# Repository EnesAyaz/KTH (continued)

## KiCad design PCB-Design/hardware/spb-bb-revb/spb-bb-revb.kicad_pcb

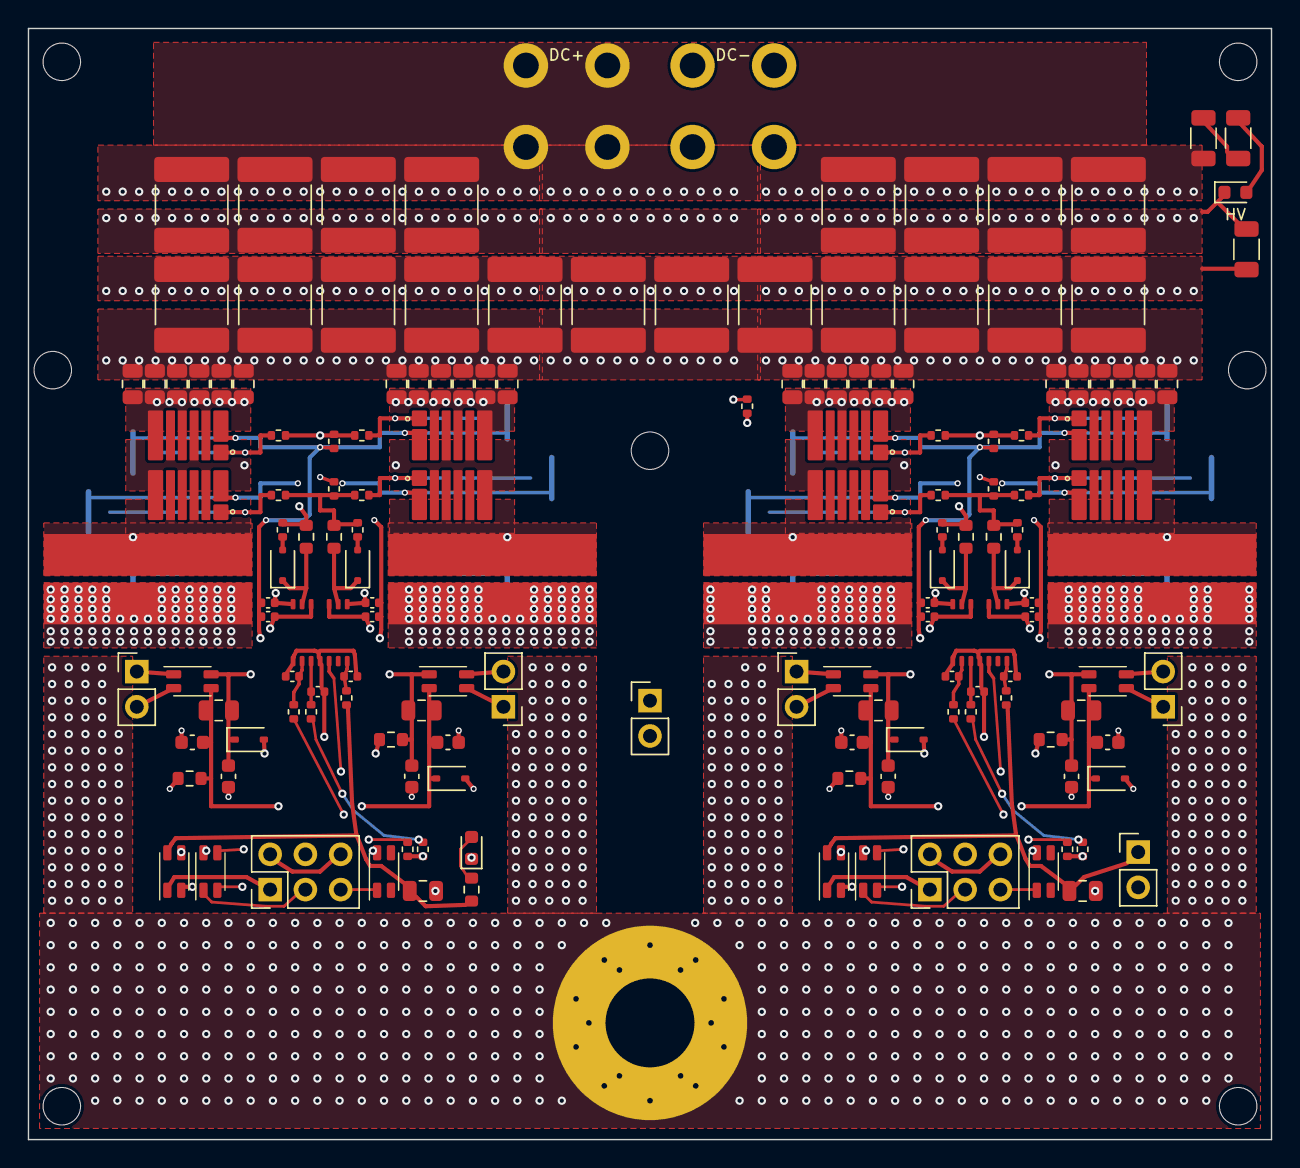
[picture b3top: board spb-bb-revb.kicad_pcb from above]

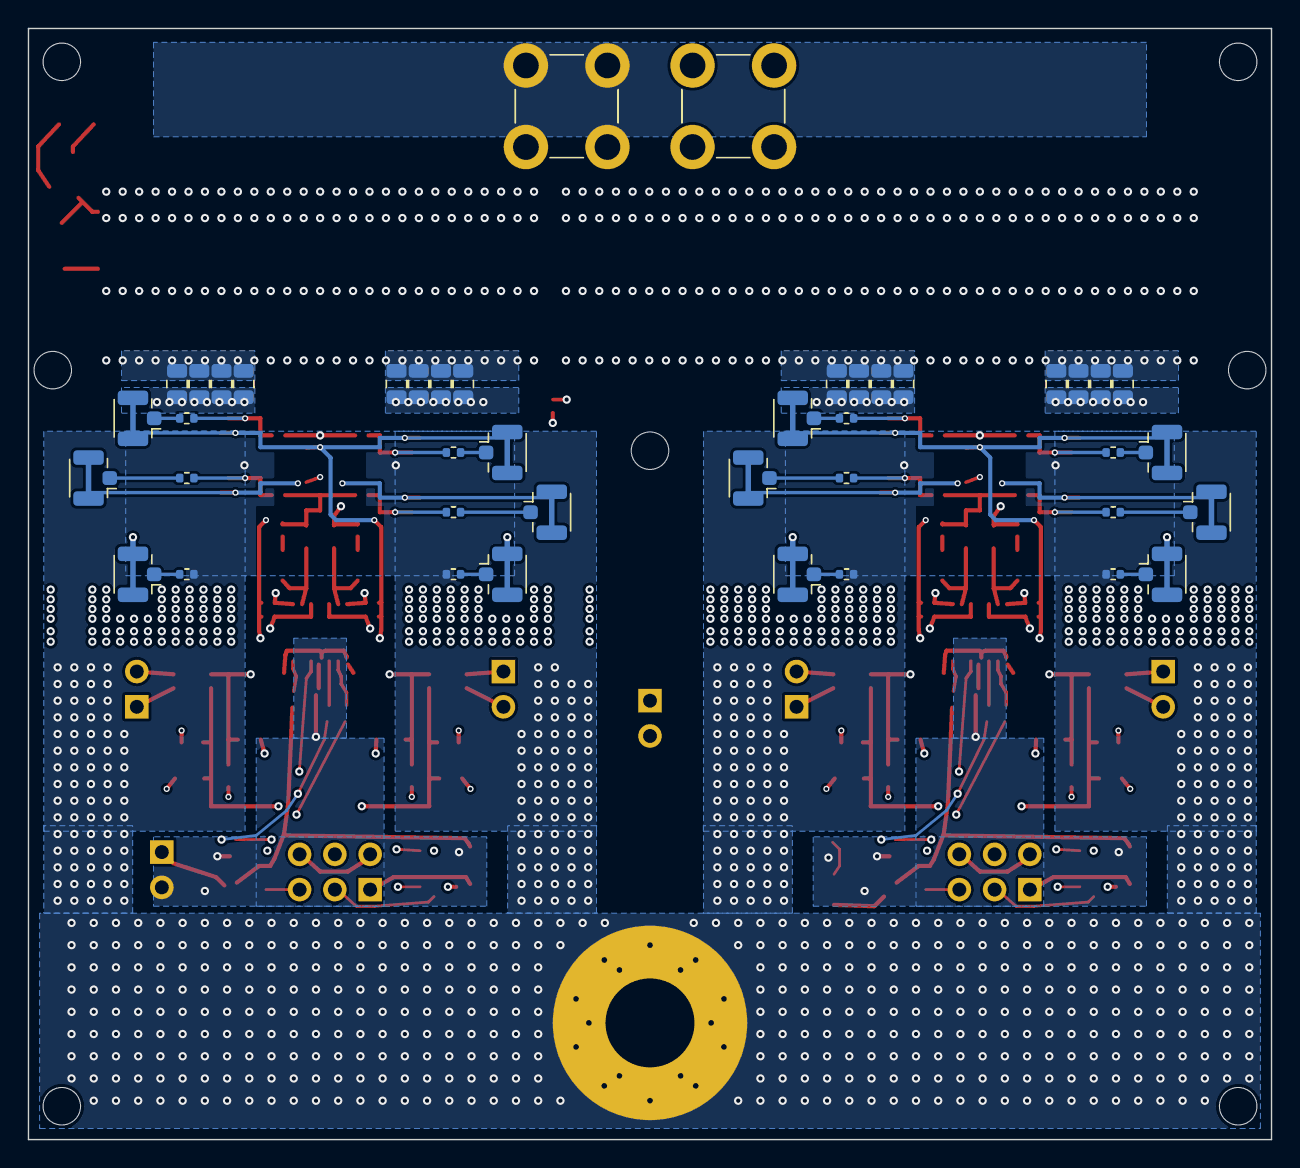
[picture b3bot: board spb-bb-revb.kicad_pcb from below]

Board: 4 copper layers, 89.5 x 80.0 mm, 204 parts (42 on the bottom side), 89 nets.

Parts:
C1, C2, C3, C4, C5, C6, C7, C8, C9, C10, C11, C12, C27, C28, C29, C30, C31, C32, C33, C34, C35, C36, C37, C38, C39, C40, C41, C42, C43, C44, C45, C46, C61, C62, C63, C64, C65, C66, C67, C68: 1uF 100V X7S; C_0805_2012Metric_TightCrtYd
C13, C14, C15, C16, C47, C48, C49, C50: 1uF 16V X7R 0402; C_0402_1005Metric
C17, C18, C51, C52: 100pF C0G 0402; C_0402_1005Metric
C19, C53: 22nF 25V X7R 0402; C_0402_1005Metric
C20, C23, C54, C57: 4.7uF 25V X7R 0805; C_0805_2012Metric
C21, C22, C24, C25, C55, C56, C58, C59: 4.7uF 16V X5R 0603; C_0603_1608Metric
C26, C60: 4.7uF 25V X7R 0805 (12 V); C_0805_2012Metric
C69, C70, C71, C72, C73, C74, C75, C76, C77, C78, C79, C80, C81, C82, C83, C84, C85, C86, C87, C88: 22uF 100V X7S 2220; C_2220_5750Metric_TightCrtYd
D1, D2, D6, D7: PMEG3020EJ; D_SOD-323F
D3, D4, D8, D9: BZX384-C5V1; D_SOD-323
D5: green 0603 (12 V); LED_0603_1608Metric
D10: red 0603 (DC link present); LED_0603_1608Metric
H1, H2, H3, H4: M2.5 insulated; MountingHole_2.7mm_M2.5
H5, H6, H7: M2.5 heatsink spreader; MountingHole_2.7mm_M2.5
HS1: Fischer LAM 4 (100 mm) + spreader; HS_LAM4K10012_revb
J1: DC+; Wuerth_REDCUBE-THR_WP-THRBU_74650174_THR
J2: DC-; Wuerth_REDCUBE-THR_WP-THRBU_74650174_THR
J3, J12: V_ISO,HS in: 1 +, 2 -; PinHeader_1x02_P2.54mm_Vertical
J4, J13: V_ISO,LS in: 1 +, 2 -; PinHeader_1x02_P2.54mm_Vertical
J5: CTRL1: 1 12V 2 GND 3 PWM_H 4 PWM_L 5 DIS 6 GND; PinHeader_2x03_P2.54mm_Vertical
J6: U.FL H1; U.FL_Hirose_U.FL-R-SMT-1_Vertical
J7: U.FL L1; U.FL_Hirose_U.FL-R-SMT-1_Vertical
J8: U.FL D1; U.FL_Hirose_U.FL-R-SMT-1_Vertical
J9: U.FL H2; U.FL_Hirose_U.FL-R-SMT-1_Vertical
J10: U.FL L2; U.FL_Hirose_U.FL-R-SMT-1_Vertical
J11: U.FL D2; U.FL_Hirose_U.FL-R-SMT-1_Vertical
J14: CTRL2: 1 12V 2 GND 3 PWM_H 4 PWM_L 5 DIS 6 GND; PinHeader_2x03_P2.54mm_Vertical
J15: FAN 12V: 1 +12V, 2 GND; PinHeader_1x02_P2.54mm_Vertical
J16: U.FL H3; U.FL_Hirose_U.FL-R-SMT-1_Vertical
J17: U.FL L3; U.FL_Hirose_U.FL-R-SMT-1_Vertical
J18: U.FL D3; U.FL_Hirose_U.FL-R-SMT-1_Vertical
J19: U.FL H4; U.FL_Hirose_U.FL-R-SMT-1_Vertical
J20: U.FL L4; U.FL_Hirose_U.FL-R-SMT-1_Vertical
J21: U.FL D4; U.FL_Hirose_U.FL-R-SMT-1_Vertical
J22: AC; AC_BOLT_M6
J23: 1:NTC 2:DC- (LS domain!); PinHeader_1x02_P2.54mm_Vertical
L1, L2, L3, L4, L5, L6, L7, L8, L9, L10: WE-CNSW 744232601; L_CommonMode_Wurth_WE-CNSW-1206
Q1, Q2, Q3, Q4, Q5, Q6, Q7, Q8: EPC2361
R1, R25: 0R5 1% (R_G HL); R_0402_1005Metric
R2, R26: 0R5 1% (R_G HR); R_0402_1005Metric
R3, R27: 0R5 1% (R_G LL); R_0402_1005Metric
R4, R28: 0R5 1% (R_G LR); R_0402_1005Metric
R5, R29: 10k 1% (HS gate pull-down); R_0402_1005Metric
R6, R30: 10k 1% (LS gate pull-down); R_0402_1005Metric
R7, R31: 0R75 1% (R_ON,A); R_0603_1608Metric
R8, R32: 0R (R_OFF,A); R_0402_1005Metric
R9, R33: 0R75 1% (R_ON,B); R_0603_1608Metric
R10, R34: 0R (R_OFF,B); R_0402_1005Metric
R11, R35: 47R 1% (INA); R_0402_1005Metric
R12, R36: 47R 1% (INB); R_0402_1005Metric
R13, R37: 3k 1% (RVDDI); R_0402_1005Metric
R14, R15, R38, R39: 150R 1% 0603 (bias, <= 82 mW); R_0603_1608Metric
R16, R40: 10k (PWM_H pull-down); R_0402_1005Metric
R17, R41: 10k (PWM_L pull-down); R_0402_1005Metric
R18: 4.7k (LED); R_0603_1608Metric
R19, R22, R42, R45: 0R (V_GS HS); R_0402_1005Metric
R20, R23, R43, R46: 0R (V_GS LS); R_0402_1005Metric
R21, R24, R44, R47: 953R 1% (V_DS LS, 20:1 into 50 R); R_0402_1005Metric
R48, R49: 68k 1206 (HV LED); R_1206_3216Metric
R50: 100k 1206 (bleeder); R_1206_3216Metric
RS1, RS2, RS3, RS4: UFCS-R001; PMK_UFCS_R001
RT1: NTC 10k B3380; R_0402_1005Metric
U1, U2: 2EDF7275K; 2EDF7275K_PG-TFLGA-13-4

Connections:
+12V1: C26.1, L3.2, R13.1, R18.1
+12V2: C60.1, J15.1, L8.2, R37.1
C_12V1: J5.1, L3.1
C_12V2: J14.1, L8.1
C_DIS1: J5.5, L5.1
C_DIS2: J14.5, L10.1
C_GND1: J5.2, J5.6, L3.4
C_GND2: J14.2, J14.6, L8.4
C_PWMH1: J5.3, L4.1
C_PWMH2: J14.3, L9.1
C_PWML1: J5.4, L4.4
C_PWML2: J14.4, L9.4
DCN: C1.2, C2.2, C3.2, C4.2, C5.2, C6.2, C7.2, C8.2, C9.2, C10.2, C11.2, C12.2, C27.1, C28.1, C29.1, C30.1, C31.1, C32.1, C33.1, C34.1, C35.2, C36.2, C37.2, C38.2, C39.2, C40.2, C41.2, C42.2, C43.2, C44.2, C45.2, C46.2, C61.1, C62.1, C63.1, C64.1, C65.1, C66.1, C67.1, C68.1, C69.1, C70.1, C71.1, C72.1, C73.1, C74.1, C75.1, C76.1, C77.1, C78.1, C79.1, C80.1, C81.1, C82.1, C83.1, C84.1, C85.1, C86.1, C87.1, C88.1, D10.1, J2.1, J23.2, R50.2, RS1.2, RS2.2, RS3.2, RS4.2, RT1.1
DCP: C1.1, C2.1, C3.1, C4.1, C5.1, C6.1, C7.1, C8.1, C9.1, C10.1, C11.1, C12.1, C27.2, C28.2, C29.2, C30.2, C31.2, C32.2, C33.2, C34.2, C35.1, C36.1, C37.1, C38.1, C39.1, C40.1, C41.1, C42.1, C43.1, C44.1, C45.1, C46.1, C61.2, C62.2, C63.2, C64.2, C65.2, C66.2, C67.2, C68.2, C69.2, C70.2, C71.2, C72.2, C73.2, C74.2, C75.2, C76.2, C77.2, C78.2, C79.2, C80.2, C81.2, C82.2, C83.2, C84.2, C85.2, C86.2, C87.2, C88.2, J1.1, Q1.3, Q1.5, Q1.7, Q2.3, Q2.5, Q2.7, Q5.3, Q5.5, Q5.7, Q6.3, Q6.5, Q6.7, R48.1, R50.1
DIS1: L5.2, U1.5
DIS2: L10.2, U2.5
GH_L1: Q1.1, R1.1, R19.2
GH_L2: Q5.1, R25.1, R42.2
GH_R1: Q2.1, R2.2, R22.1
GH_R2: Q6.1, R26.2, R45.1
GH_STAR1: R1.2, R2.1, R5.2, R7.2, R8.2
GH_STAR2: R25.2, R26.1, R29.2, R31.2, R32.2
GL_L1: Q3.1, R3.1, R20.2
GL_L2: Q7.1, R27.1, R43.2
GL_R1: Q4.1, R4.2, R23.1
GL_R2: Q8.1, R28.2, R46.1
GL_STAR1: R3.2, R4.1, R6.1, R9.2, R10.2
GL_STAR2: R27.2, R28.1, R30.1, R33.2, R34.2
GNDI1: C17.1, C18.2, C19.2, C26.2, D5.1, L3.3, R16.1, R17.1, U1.1, U1.4
GNDI2: C51.1, C52.2, C53.2, C60.2, J15.2, L8.3, R40.1, R41.1, U2.1, U2.4
HVA: R48.2, R49.1
HVB: D10.2, R49.2
INA1: C17.2, R11.2, U1.2
INA2: C51.2, R35.2, U2.2
INB1: C18.1, R12.2, U1.3
INB2: C52.1, R36.2, U2.3
KH1: C13.1, C14.1, C21.1, C22.1, D3.2, J6.2, J9.2, Q1.2, Q2.2, R5.1, R14.1
KH2: C47.1, C48.1, C55.1, C56.1, D8.2, J16.2, J19.2, Q5.2, Q6.2, R29.1, R38.1
KL1: C15.2, C16.2, C24.1, C25.2, D4.2, J7.2, J10.2, Q3.2, Q4.2, R6.2, R15.1
KL2: C49.2, C50.2, C58.1, C59.2, D9.2, J17.2, J20.2, Q7.2, Q8.2, R30.2, R39.1
LEDA_12V1: D5.2, R18.2
LSRC1: J8.2, Q3.4, Q3.6, RS1.1
LSRC2: J11.2, Q4.4, Q4.6, RS2.1
LSRC3: J18.2, Q7.4, Q7.6, RS3.1
LSRC4: J21.2, Q8.4, Q8.6, RS4.1
NTC: J23.1, RT1.2
OFFA1: D1.2, R8.1
OFFA2: D6.2, R32.1
OFFB1: D2.2, R10.1
OFFB2: D7.2, R34.1
OUTA1: D1.1, R7.1, U1.12
OUTA2: D6.1, R31.1, U2.12
OUTB1: D2.1, R9.1, U1.9
OUTB2: D7.1, R33.1, U2.9
PWM_H1: L4.2, R11.1, R16.2
PWM_H2: L9.2, R35.1, R40.2
PWM_L1: L4.3, R12.1, R17.2
PWM_L2: L9.3, R36.1, R41.2
SW: J22.1, Q1.4, Q1.6, Q2.4, Q2.6, Q3.3, Q3.5, Q3.7, Q4.3, Q4.5, Q4.7, Q5.4, Q5.6, Q6.4, Q6.6, Q7.3, Q7.5, Q7.7, Q8.3, Q8.5, Q8.7, R21.2, R24.1, R44.2, R47.1
UFL_D1: J8.1, R21.1
UFL_D2: J11.1, R24.2
UFL_D3: J18.1, R44.1
UFL_D4: J21.1, R47.2
UFL_H1: J6.1, R19.1
UFL_H2: J9.1, R22.2
UFL_H3: J16.1, R42.1
UFL_H4: J19.1, R45.2
UFL_L1: J7.1, R20.1
UFL_L2: J10.1, R23.2
UFL_L3: J17.1, R43.1
UFL_L4: J20.1, R46.2
VDDA1: C13.2, C20.2, C21.2, D3.1, L1.2, U1.13
VDDA2: C47.2, C54.2, C55.2, D8.1, L6.2, U2.13
VDDB1: C16.1, C23.2, C25.1, D4.1, L2.4, U1.10
VDDB2: C50.1, C57.2, C59.1, D9.1, L7.4, U2.10
VDDI1: C19.1, R13.2, U1.7
VDDI2: C53.1, R37.2, U2.7
VEEA1: C14.2, C20.1, C22.2, L1.3, R14.2, U1.11
VEEA2: C48.2, C54.1, C56.2, L6.3, R38.2, U2.11
VEEB1: C15.1, C23.1, C24.2, L2.1, R15.2, U1.8
VEEB2: C49.1, C57.1, C58.2, L7.1, R39.2, U2.8
VINA_N1: J3.2, L1.4
VINA_N2: J12.2, L6.4
VINA_P1: J3.1, L1.1
VINA_P2: J12.1, L6.1
VINB_N1: J4.2, L2.2
VINB_N2: J13.2, L7.2
VINB_P1: J4.1, L2.3
VINB_P2: J13.1, L7.3

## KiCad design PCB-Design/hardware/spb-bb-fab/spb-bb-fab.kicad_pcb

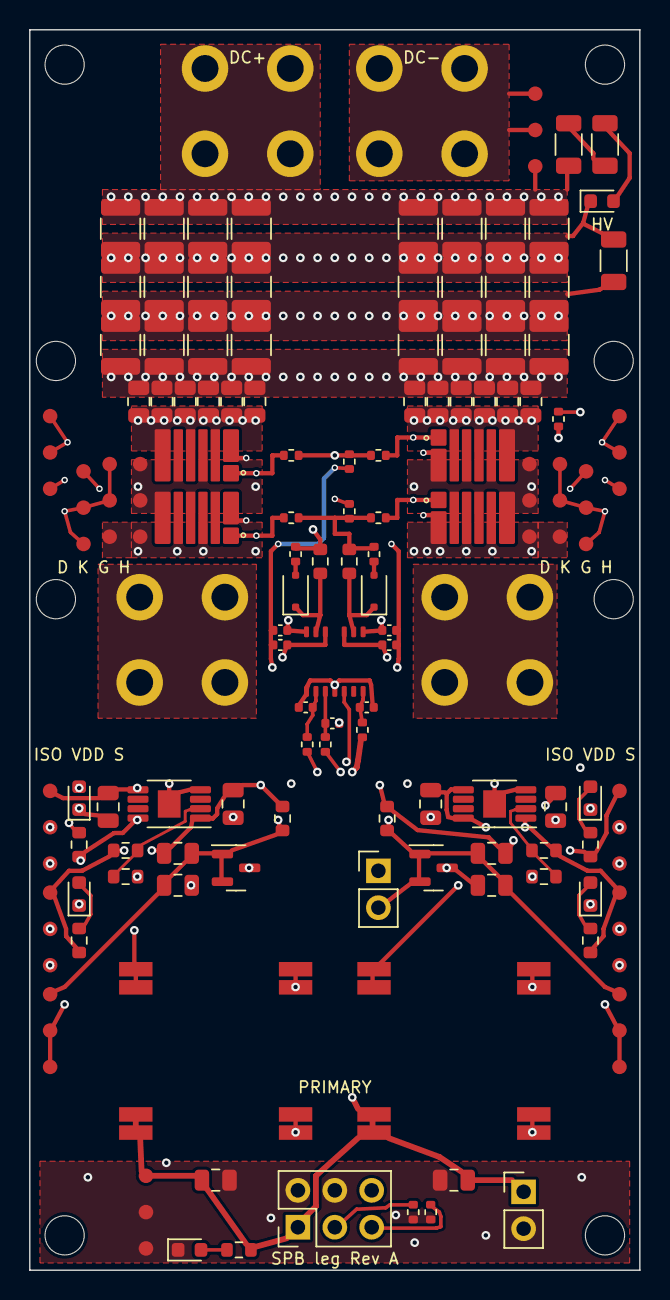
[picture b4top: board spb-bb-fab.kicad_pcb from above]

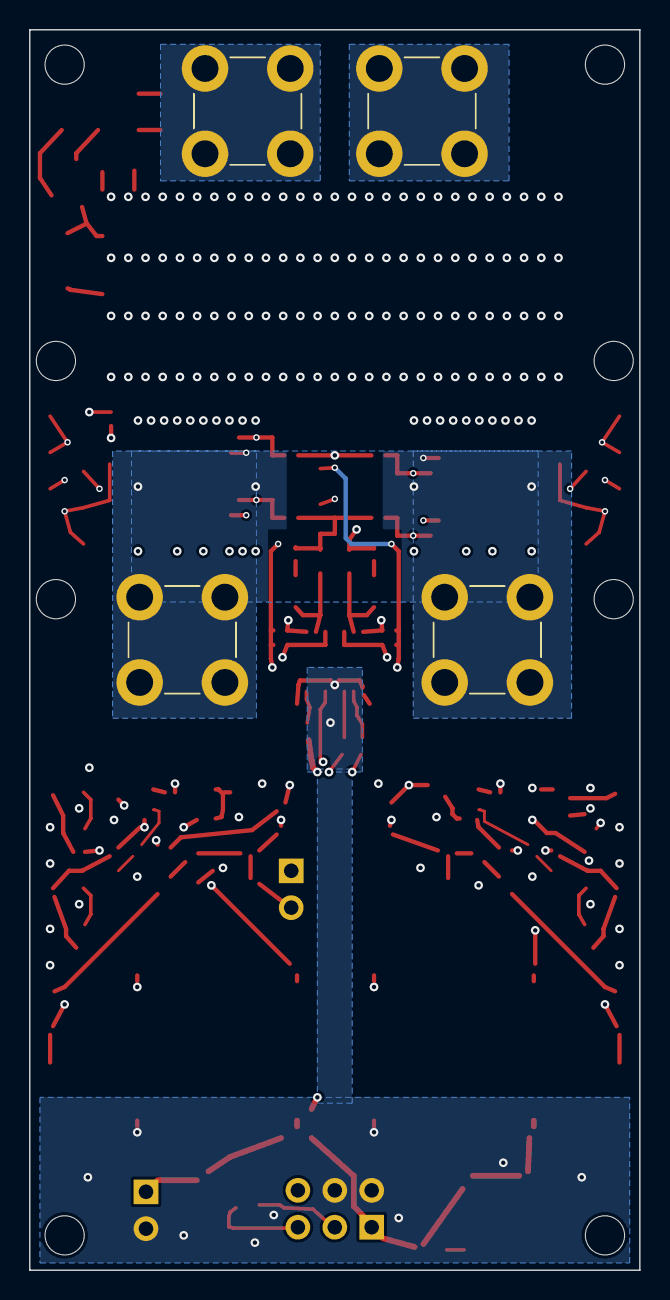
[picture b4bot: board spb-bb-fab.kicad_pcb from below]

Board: 4 copper layers, 42.0 x 85.4 mm, 134 parts (4 on the bottom side), 37 nets.

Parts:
C1, C2, C3, C4, C5, C6, C7, C8, C9, C10, C11, C12: 1uF 100V X7S; C_0805_2012Metric_TightCrtYd
C13, C14, C15, C16, C17, C18, C19, C20, C21, C22, C23, C24, C25, C26, C27, C28, C29, C30, C31, C32, C33, C34, C35, C36: 10uF 100V X7S; C_1210_3225Metric_TightCrtYd
C100, C101, C102, C103: 1uF 16V X7R 0402; C_0402_1005Metric
C104, C105: 100pF C0G 0402; C_0402_1005Metric
C106: 22nF 25V X7R 0402; C_0402_1005Metric
C107, C112: 4.7uF 25V X7R 0805; C_0805_2012Metric
C108, C113: 10uF 16V X7R 0805; C_0805_2012Metric
C109, C110, C114, C115: 4.7uF 16V X7R 0805; C_0805_2012Metric
C111, C116: 4.7uF 25V X7R 0805 (12 V in); C_0805_2012Metric
D1, D2: PMEG3020EJ; D_SOD-323F
D3: green 0603 (ISO A); LED_0603_1608Metric
D4: green 0603 (VDD A); LED_0603_1608Metric
D5: green 0603 (ISO B); LED_0603_1608Metric
D6: green 0603 (VDD B); LED_0603_1608Metric
D7: green 0603 (12 V); LED_0603_1608Metric
D8: red 0603 (DC link present); LED_0603_1608Metric
H1, H2, H3, H4: M2.5 insulated; MountingHole_2.7mm_M2.5
H5, H6, H7, H8: M2.5 heatsink; MountingHole_2.7mm_M2.5
HS1: Fischer LAM 4 K 50 12 + spreader; HS_LAM4K5012_assembly
J1: DC+; Wuerth_REDCUBE-THR_WP-THRBU_74650174_THR
J2: DC-; Wuerth_REDCUBE-THR_WP-THRBU_74650174_THR
J3, J4: AC; Wuerth_REDCUBE-THR_WP-THRBU_74650174_THR
J5: 1:+12V 2:GND 3:PWM_H 4:GND 5:PWM_L 6:DIS; PinHeader_2x03_P2.54mm_Vertical
J6: 1:NTC 2:DC- (LS domain!); PinHeader_1x02_P2.54mm_Vertical
J7: FAN 12V: 1 +12V, 2 GND; PinHeader_1x02_P2.54mm_Vertical
PS1, PS2: MGN1S1208MC; Murata_MGN1_SMD
Q1, Q2, Q3, Q4: EPC2361
R1: 0R5 1% (gate HL); R_0402_1005Metric
R2: 0R5 1% (gate HR); R_0402_1005Metric
R3: 0R5 1% (gate LL); R_0402_1005Metric
R4: 0R5 1% (gate LR); R_0402_1005Metric
R5: 0R75 1% (R_ON,A); R_0603_1608Metric
R6: 0R (R_OFF,A); R_0402_1005Metric
R7: 0R75 1% (R_ON,B); R_0603_1608Metric
R8: 0R (R_OFF,B); R_0402_1005Metric
R9: 47R 1% (INA); R_0402_1005Metric
R10: 47R 1% (INB); R_0402_1005Metric
R11: 3k 1% (RVDDI); R_0402_1005Metric
R12, R15: 102k 1%; R_0603_1608Metric
R13, R16: 23.7k 1%; R_0603_1608Metric
R14, R17: 2.2k 1% (shunt bias); R_0603_1608Metric
R30, R32: 2.7k (LED); R_0603_1608Metric
R31, R33: 1.8k (LED); R_0603_1608Metric
R34: 4.7k (LED); R_0603_1608Metric
R35: 10k (PWM_H pull-down); R_0402_1005Metric
R36: 10k (PWM_L pull-down); R_0402_1005Metric
R37, R38: 68k 1206 (HV LED); R_1206_3216Metric
R39: 100k 1206 (bleeder); R_1206_3216Metric
R41: 10k 1% (HS gate pull-down); R_0402_1005Metric
R42: 10k 1% (LS gate pull-down); R_0402_1005Metric
RT1: NTC 10k B3380; R_0402_1005Metric
TP1: D: Vds Q3; Probe_2Sig1Gnd_2.5_5.0
TP2: K: vKS Q3 (tip K); Probe_2Sig1Gnd_2.5_5.0
TP3: G: Vgs Q3; Probe_1Sig2Gnd_2.5_5.0
TP4: H: Vgs Q1 (iso); Probe_1Sig2Gnd_2.5_5.0
TP5: D: Vds Q4; Probe_2Sig1Gnd_2.5_5.0
TP6: K: vKS Q4 (tip K); Probe_2Sig1Gnd_2.5_5.0
TP7: G: Vgs Q4; Probe_1Sig2Gnd_2.5_5.0
TP8: H: Vgs Q2 (iso); Probe_1Sig2Gnd_2.5_5.0
TP9: ISO A; Probe_1Sig2Gnd_2.5_5.0
TP10: VDD A; Probe_1Sig2Gnd_2.5_5.0
TP11: S A; Probe_1Sig2Gnd_2.5_5.0
TP12: ISO B; Probe_1Sig2Gnd_2.5_5.0
TP13: VDD B; Probe_1Sig2Gnd_2.5_5.0
TP14: S B; Probe_1Sig2Gnd_2.5_5.0
TP15: 12V; Probe_1Sig2Gnd_2.5_5.0
TP16: DC link; Probe_1Sig2Gnd_2.5_5.0
U1: 2EDF7275K; 2EDF7275K_PG-TFLGA-13-4
U2, U3: TPS7A4901 6.29 V; HVSSOP-8-1EP_3x3mm_P0.65mm_EP1.57x1.89mm
U4, U5: TLV431A (1.24 V); SOT-23

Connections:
+12V: C111.1, C116.2, J5.1, J7.1, PS1.19, PS1.20, PS2.19, PS2.20, R11.1, R34.2, TP15.1
ADJA: R12.2, R13.1, U2.2
ADJB: R15.1, R16.2, U3.2
DCN: C1.2, C2.2, C3.2, C4.2, C5.2, C6.2, C7.2, C8.2, C9.2, C10.2, C11.2, C12.2, C13.1, C14.1, C15.1, C16.1, C17.1, C18.1, C19.1, C20.1, C21.2, C22.2, C23.2, C24.2, C25.2, C26.2, C27.2, C28.2, C29.1, C30.1, C31.1, C32.1, C33.1, C34.1, C35.1, C36.1, C102.2, C103.2, C114.1, C115.2, D8.1, J2.1, J6.2, Q3.2, Q3.4, Q3.6, Q4.2, Q4.4, Q4.6, R17.1, R39.2, R42.2, RT1.1, TP1.2, TP2.1, TP2.2, TP3.2, TP5.2, TP6.1, TP6.2, TP7.2, TP14.1, TP16.2, U5.1, U5.2
DCP: C1.1, C2.1, C3.1, C4.1, C5.1, C6.1, C7.1, C8.1, C9.1, C10.1, C11.1, C12.1, C13.2, C14.2, C15.2, C16.2, C17.2, C18.2, C19.2, C20.2, C21.1, C22.1, C23.1, C24.1, C25.1, C26.1, C27.1, C28.1, C29.2, C30.2, C31.2, C32.2, C33.2, C34.2, C35.2, C36.2, J1.1, Q1.3, Q1.5, Q1.7, Q2.3, Q2.5, Q2.7, R37.1, R39.1, TP16.1
DIS: J5.6, U1.5
GH_L: Q1.1, R1.1, TP4.1
GH_R: Q2.1, R2.2, TP8.1
GH_STAR: R1.2, R2.1, R5.2, R6.2, R41.2
GL_L: Q3.1, R3.1, TP3.1
GL_R: Q4.1, R4.2, TP7.1
GL_STAR: R3.2, R4.1, R7.2, R8.2, R42.1
GNDI: C104.1, C105.2, C106.2, C111.2, C116.1, D7.1, J5.2, J5.4, J7.2, PS1.1, PS1.2, PS2.1, PS2.2, R35.1, R36.1, TP15.2, U1.1, U1.4
HVA: R37.2, R38.1
HVB: D8.2, R38.2
INA: C104.2, R9.2, U1.2
INB: C105.1, R10.2, U1.3
ISOA_P: C107.2, PS1.11, PS1.12, R30.1, TP9.1, U2.5, U2.8
ISOB_P: C112.2, PS2.11, PS2.12, R32.1, TP12.1, U3.5, U3.8
LEDA_12V: D7.2, R34.1
LEDA_ISOA: D3.2, R30.2
LEDA_ISOB: D5.2, R32.2
LEDA_VDDA: D4.2, R31.2
LEDA_VDDB: D6.2, R33.2
NTC: J6.1, RT1.2
OFFA: D1.2, R6.1
OFFB: D2.2, R8.1
OUTA: D1.1, R5.1, U1.12
OUTB: D2.1, R7.1, U1.9
PWM_H: J5.3, R9.1, R35.2
PWM_L: J5.5, R10.1, R36.2
SW: C100.1, C101.1, C109.2, C110.1, J3.1, J4.1, Q1.2, Q1.4, Q1.6, Q2.2, Q2.4, Q2.6, Q3.3, Q3.5, Q3.7, Q4.3, Q4.5, Q4.7, R14.1, R41.1, TP1.1, TP4.2, TP5.1, TP8.2, TP11.1, U4.1, U4.2
VDDA: C100.2, C108.2, C109.1, R12.1, R14.2, R31.1, TP10.1, U1.13, U2.1
VDDB: C103.1, C113.2, C114.2, R15.2, R17.2, R33.1, TP13.1, U1.10, U3.1
VDDI: C106.1, R11.2, U1.7
VEEA: C101.2, C107.1, C108.1, C110.2, D3.1, D4.1, PS1.9, PS1.10, R13.2, TP9.2, TP10.2, TP11.2, U1.11, U2.4, U2.9, U4.3
VEEB: C102.1, C112.1, C113.1, C115.1, D5.1, D6.1, PS2.9, PS2.10, R16.1, TP12.2, TP13.2, TP14.2, U1.8, U3.4, U3.9, U5.3

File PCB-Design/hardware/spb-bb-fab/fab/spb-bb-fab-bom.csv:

Qty,References,Value,Footprint,Manufacturer part / note
4,Q1 Q3 Q2 Q4,EPC2361,EPC2361,EPC2361
12,C1 C2 C3 C4 C5 C6 C7 C8 C9 C10 C11 C12,1uF 100V X7S,C_0805_2012Metric_TightCrtYd,TDK C2012X7S2A105K125AB
24,C13 C14 C15 C16 C17 C18 C19 C20 C21 C22 C23 C24 C25 C26 C27 C28 C29 C30 C31 C32 C33 C34 C35 C36,10uF 100V X7S,C_1210_3225Metric_TightCrtYd,Murata GRM32EC72A106KE05L
4,R1 R2 R3 R4,0R5 1% (gate HL),R_0402_1005Metric,0.5R 0402 1% (Panasonic ERJ-2BQFR50X)
4,R41 R42 R35 R36,10k 1% (HS gate pull-down),R_0402_1005Metric,10k 0402 1%
1,U1,2EDF7275K,2EDF7275K_PG-TFLGA-13-4,Infineon 2EDF7275KXUMA1
2,R5 R7,"0R75 1% (R_ON,A)",R_0603_1608Metric,0.75R 0603 1% (Panasonic ERJ-3RQFR75V)
2,R6 R8,"0R (R_OFF,A)",R_0402_1005Metric,0R 0402 jumper (set R_OFF here)
2,D1 D2,PMEG3020EJ,D_SOD-323F,"Nexperia PMEG3020EJ (30 V, 2 A, SOD323F)"
4,C100 C101 C102 C103,1uF 16V X7R 0402,C_0402_1005Metric,Murata GRM155R71C105KA12
2,C104 C105,100pF C0G 0402,C_0402_1005Metric,Murata GRM1555C1H101JA01
1,C106,22nF 25V X7R 0402,C_0402_1005Metric,Murata GRM155R71E223KA61
2,R9 R10,47R 1% (INA),R_0402_1005Metric,47R 0402 1%
1,R11,3k 1% (RVDDI),R_0402_1005Metric,3.0k 0402 1%
2,PS1 PS2,MGN1S1208MC,Murata_MGN1_SMD,Murata MGN1S1208MC-R7
2,U2 U3,TPS7A4901 6.29 V,HVSSOP-8-1EP_3x3mm_P0.65mm_EP1.57x1.89mm,TI TPS7A4901DGNR
4,C107 C111 C112 C116,4.7uF 25V X7R 0805,C_0805_2012Metric,Murata GRM21BR71E475KA73
2,C108 C113,10uF 16V X7R 0805,C_0805_2012Metric,Murata GRM21BR71C106KE51
2,R12 R15,102k 1%,R_0603_1608Metric,102k 0603 1%
2,R13 R16,23.7k 1%,R_0603_1608Metric,23.7k 0603 1%
4,C109 C110 C114 C115,4.7uF 16V X7R 0805,C_0805_2012Metric,Murata GRM21BR71C475KA73
2,U4 U5,TLV431A (1.24 V),SOT-23,TI TLV431AIDBZR
2,R14 R17,2.2k 1% (shunt bias),R_0603_1608Metric,2.2k 0603 1%
4,J1 J2 J3 J4,DC+,Wuerth_REDCUBE-THR_WP-THRBU_74650174_THR,"Wuerth 74650174 (REDCUBE THR, M4)"
1,J5,1:+12V 2:GND 3:PWM_H 4:GND 5:PWM_L 6:DIS,PinHeader_2x03_P2.54mm_Vertical,2.54 mm header 2x3
1,J6,1:NTC 2:DC- (LS domain!),PinHeader_1x02_P2.54mm_Vertical,2.54 mm header 1x2
1,RT1,NTC 10k B3380,R_0402_1005Metric,Murata NCP15XH103F03RC
5,D3 D4 D5 D6 D7,green 0603 (ISO A),LED_0603_1608Metric,Wurth 150060GS75000
2,R30 R32,2.7k (LED),R_0603_1608Metric,2.7k 0603 1%
2,R31 R33,1.8k (LED),R_0603_1608Metric,1.8k 0603 1%
1,R34,4.7k (LED),R_0603_1608Metric,4.7k 0603 1%
1,J7,"FAN 12V: 1 +12V, 2 GND",PinHeader_1x02_P2.54mm_Vertical,2.54 mm header 1x2 (fan)
2,R37 R38,68k 1206 (HV LED),R_1206_3216Metric,68k 1206 1% 200 V
1,D8,red 0603 (DC link present),LED_0603_1608Metric,Wurth 150060RS75000
1,R39,100k 1206 (bleeder),R_1206_3216Metric,100k 1206 1% 200 V

Mechanical / thermal (not placed by the assembler)
1,HS1,"Fan heatsink 40x40x50 mm, 12 V fan",-,"Fischer Elektronik LAM 4 K 50 12 (0.65 K/W), Farnell 4708974"
1,HS1,"Heat spreader, Al 6061-T6, 42 x 14 x 3 mm, 2 pedestals 0.6 mm, 4 ears M2.5",-,"machined, drawing spb-bb-fab-spreader-drawing.pdf"
2,HS1,"Insulating gap pad over each cell, 8 x 10 mm, 0.5 mm, >= 5 W/mK",-,"Bergquist TGP 5000 (Gap Pad 5000S35) 0.020 in, cut to size, or equivalent"
1,HS1,Thermal compound spreader to heatsink,-,non-conductive silicone paste
4,H5-H8,M2.5 x 10 screw + insulating shoulder washer (heatsink),-,nylon or steel with insulating washer
4,H1-H4,M2.5 standoff + screw (board mounting),-,insulated
2,J1-J2,M4 screw for REDCUBE DC terminals,-,Wuerth WP-THRBU M4
2,J3-J4,M4 screw for REDCUBE AC terminals,-,Wuerth WP-THRBU M4
